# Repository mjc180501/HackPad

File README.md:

### Challenges
I had never made a PCB before. I struggled to route it correctly because I initially did not know to route on both sides, so I was frustrated when I couldn't route the whole thing on the same side. 

### Inspiration
I used Hack Club's design as a baseline but added an additional key and connected each of the 5 keys to a keyboard shortcut in order to speed up my workflow when coding. Thanks to the HackPad tutorial for being descriptive and clear.  

### Screenshot of Hackpad:

### Schematic:

### PCB:

### Case:

### BOM:
4x Cherry MX Switches

2x SK6812 MINI Leds

5x DSA Keycaps

1x XIAO RP2040

4x M3x16 Bolt

1x Case (2 3D Printed Parts)

### Others:

KMK Firmware 

Top.stl

Bottom.stl

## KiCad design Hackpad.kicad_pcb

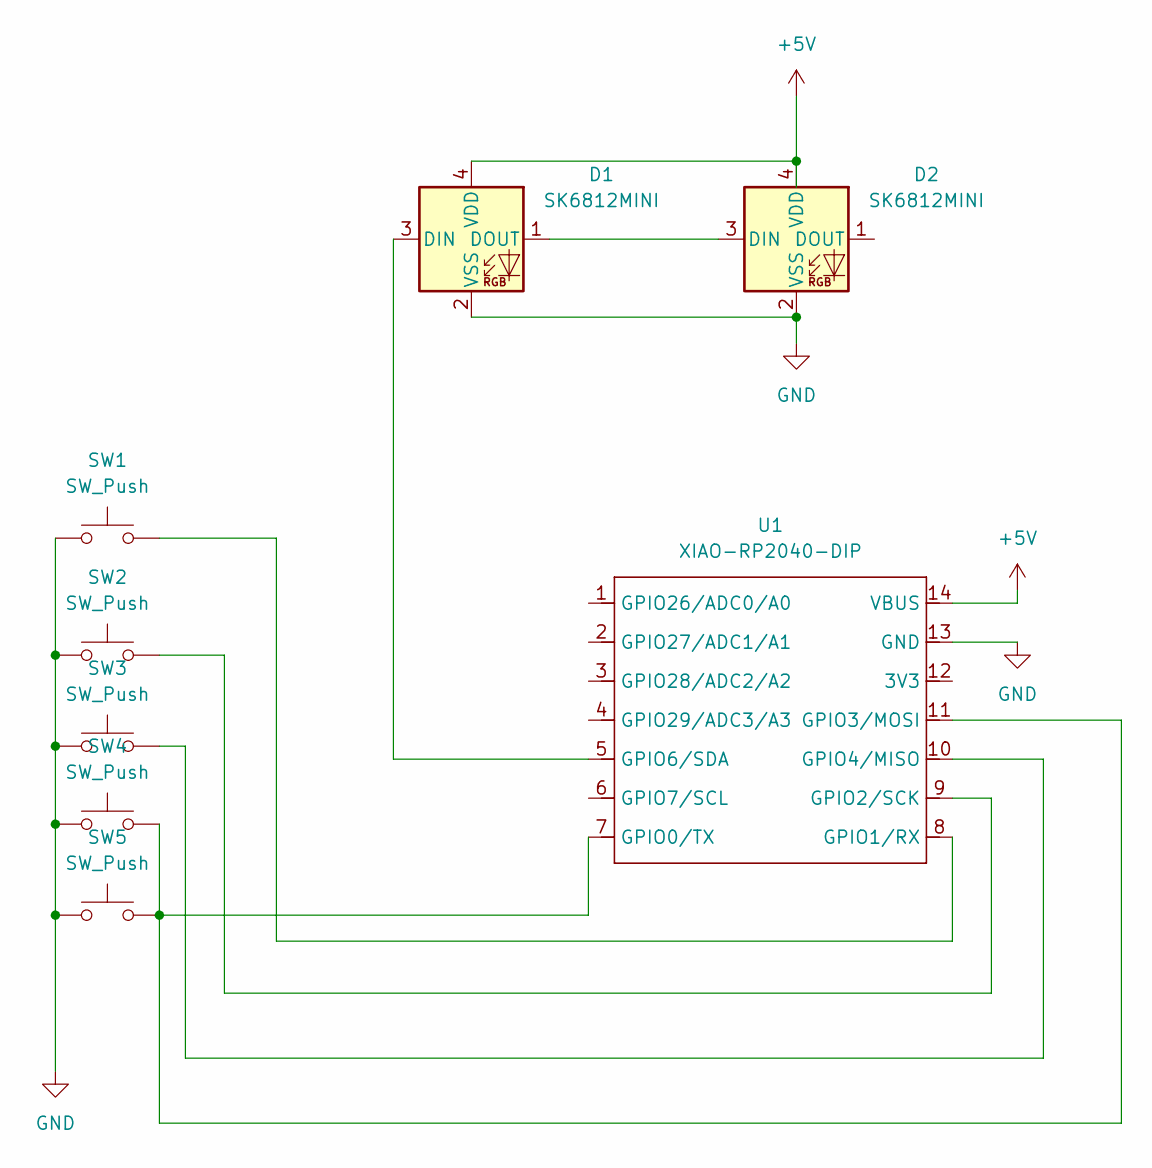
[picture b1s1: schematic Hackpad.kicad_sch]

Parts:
D1, D2: SK6812MINI; LED_SK6812MINI_PLCC4_3.5x3.5mm_P1.75mm
SW1, SW2, SW3, SW4, SW5: SW_Push; SW_Cherry_MX_1.00u_PCB
U1: XIAO-RP2040-DIP

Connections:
+5V: D1.4 (VDD), D2.4 (VDD), U1.14 (VBUS)
GND: D1.2 (VSS), D2.2 (VSS), SW1.1, SW2.1, SW3.1, SW4.1, SW5.1, U1.13 (GND)
unnamed: D1.3 (DIN), U1.5 (GPIO6/SDA)
unnamed: D1.1 (DOUT), D2.3 (DIN)
unnamed: SW4.2, SW5.2, U1.7 (GPIO0/TX), U1.11 (GPIO3/MOSI)
unnamed: SW1.2, U1.8 (GPIO1/RX)
unnamed: SW2.2, U1.9 (GPIO2/SCK)
unnamed: SW3.2, U1.10 (GPIO4/MISO)

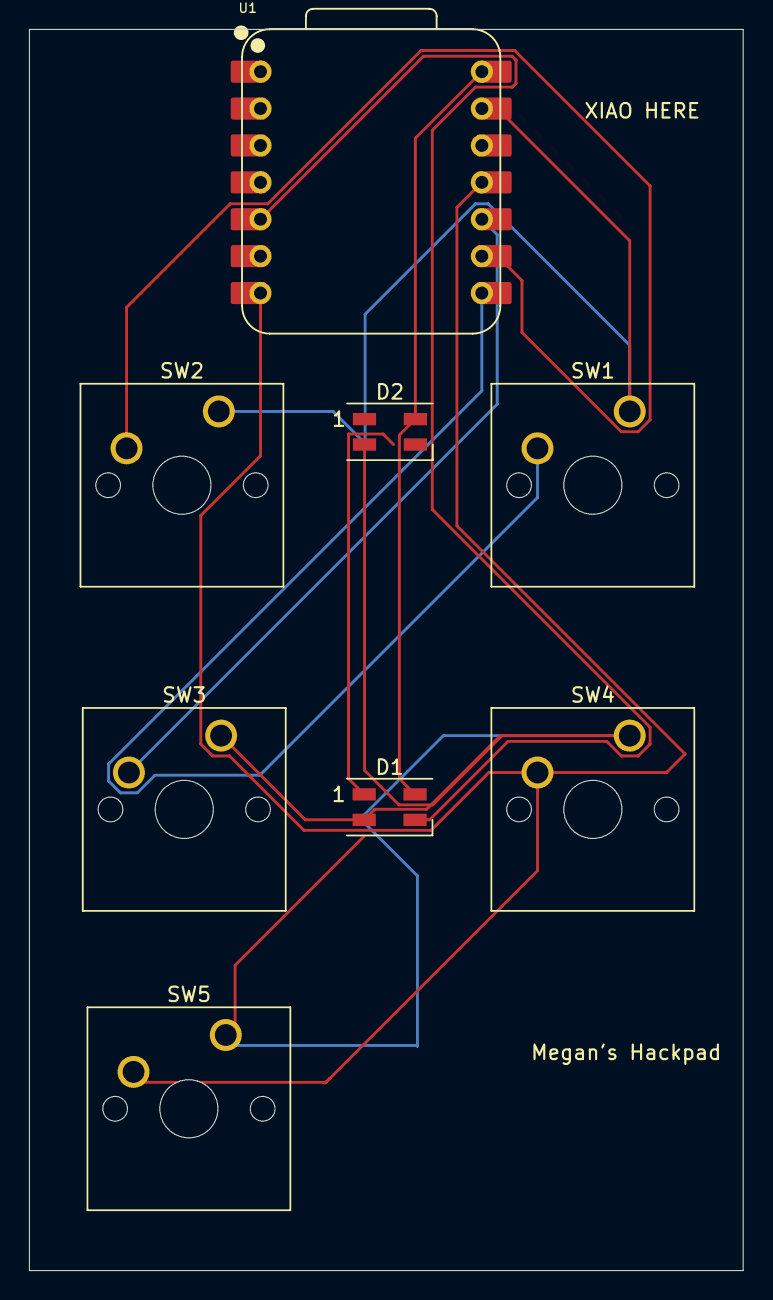
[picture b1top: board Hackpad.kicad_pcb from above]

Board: 2 copper layers, 49.1 x 85.5 mm, 8 parts (0 on the bottom side), 8 nets.

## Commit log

2025-05-26 Entire Project
2025-05-26 Updated README 2
2025-05-27 Updated README 3
2025-05-27 Updated README 4
2025-05-27 Updated README 5
2025-05-27 Update README 6
